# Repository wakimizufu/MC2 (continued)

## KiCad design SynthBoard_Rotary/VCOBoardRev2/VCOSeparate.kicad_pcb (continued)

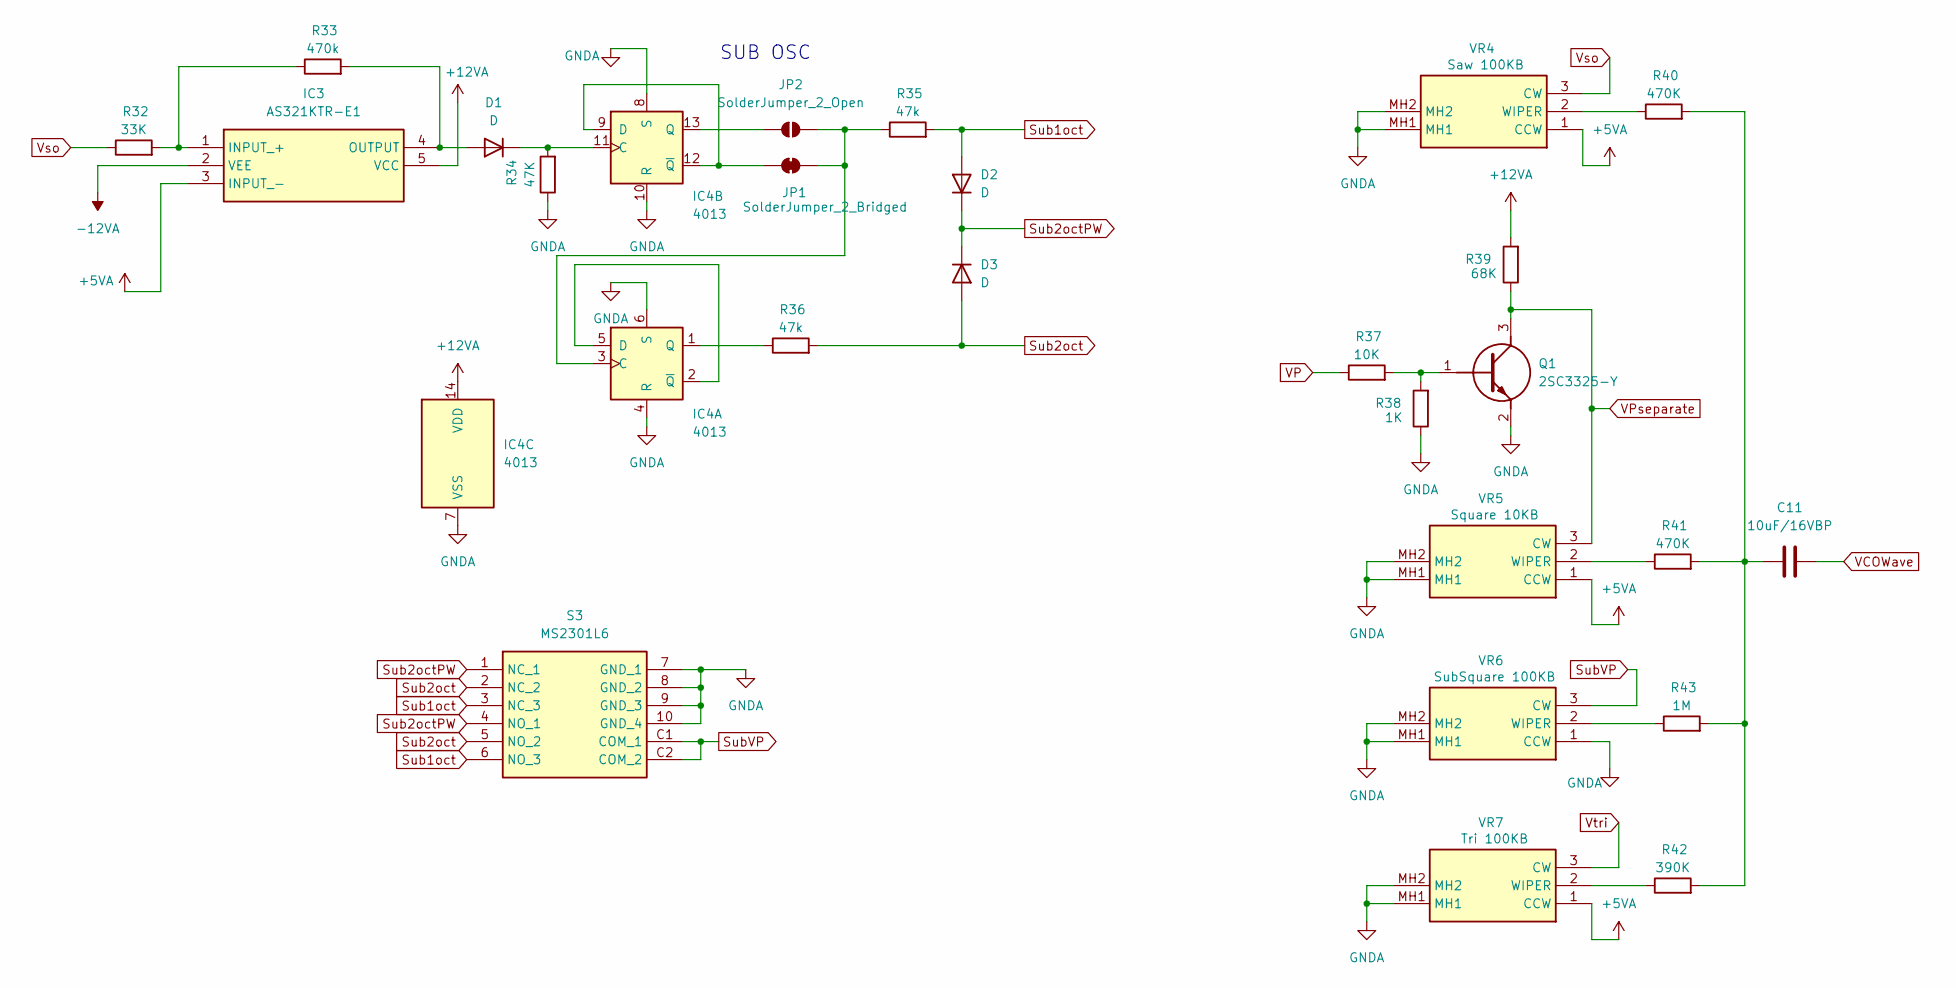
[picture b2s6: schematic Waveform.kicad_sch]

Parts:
C11: 10uF/16VBP; CP_Radial_D5.0mm_P2.50mm
D1, D2, D3: D; D_DO-15_P2.54mm_Vertical_AnodeUp
IC3: AS321KTR-E1; SOT95P282X145-5N; Manufacturer_Part_Number AS321KTR-E1; Mouser Part Number 621-AS321KTR-E1
IC4: 4013; SOIC-14_3.9x8.7mm_P1.27mm
JP1: SolderJumper_2_Bridged; SolderJumper-2_P1.3mm_Bridged2Bar_RoundedPad1.0x1.5mm
JP2: SolderJumper_2_Open; SolderJumper-2_P1.3mm_Open_RoundedPad1.0x1.5mm
Q1: 2SC3325-Y; 2SC3325YLF; Manufacturer_Part_Number 2SC3325-Y
R32: 33K; R_Axial_DIN0207_L6.3mm_D2.5mm_P2.54mm_Vertical
R33: 470k; R_Axial_DIN0207_L6.3mm_D2.5mm_P2.54mm_Vertical
R34: 47K; R_Axial_DIN0207_L6.3mm_D2.5mm_P2.54mm_Vertical
R35, R36: 47k; R_Axial_DIN0207_L6.3mm_D2.5mm_P2.54mm_Vertical
R37: 10K; R_Axial_DIN0207_L6.3mm_D2.5mm_P2.54mm_Vertical
R38: 1K; R_Axial_DIN0207_L6.3mm_D2.5mm_P2.54mm_Vertical
R39: 68K; R_Axial_DIN0207_L6.3mm_D2.5mm_P2.54mm_Vertical
R40, R41: 470K; R_Axial_DIN0207_L6.3mm_D2.5mm_P2.54mm_Vertical
R42: 390K; R_Axial_DIN0207_L6.3mm_D2.5mm_P2.54mm_Vertical
R43: 1M; R_Axial_DIN0207_L6.3mm_D2.5mm_P2.54mm_Vertical
S3: MS2301L6; Manufacturer_Part_Number MS2301L6
VR4: Saw 100KB; RK09D117000B; Manufacturer_Part_Number RK09D117000B; Mouser Part Number 688-RK09D117000B
VR5: Square 10KB; RK09D117000B; Manufacturer_Part_Number RK09D117000B; Mouser Part Number 688-RK09D117000B
VR6: SubSquare 100KB; RK09D117000B; Manufacturer_Part_Number RK09D117000B; Mouser Part Number 688-RK09D117000B
VR7: Tri 100KB; RK09D117000B; Manufacturer_Part_Number RK09D117000B; Mouser Part Number 688-RK09D117000B

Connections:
+5VA: IC3.3 (INPUT_-), VR4.1 (CCW), VR5.1 (CCW), VR7.1 (CCW); also elsewhere on the board
+12VA: IC3.5 (VCC), IC4.14 (VDD), R39.2; also elsewhere on the board
-12VA: IC3.2 (VEE); also elsewhere on the board
GNDA: IC4.4 (R), IC4.6 (S), IC4.7 (VSS), IC4.8 (S), IC4.10 (R), Q1.2 (E), R34.1, R38.1, S3.7 (GND_1), S3.8 (GND_2), S3.9 (GND_3), S3.10 (GND_4), VR4.MH1, VR4.MH2, VR5.MH1, VR5.MH2, VR6.1 (CCW), VR6.MH1, VR6.MH2, VR7.MH1, VR7.MH2; also elsewhere on the board
unnamed: C11.1, R40.2, R41.2, R42.2, R43.2
unnamed: D1.2 (A), IC3.4 (OUTPUT), R33.2
unnamed: D1.1 (K), IC4.11 (C), R34.2
unnamed: IC3.1 (INPUT_+), R32.2, R33.1
unnamed: IC4.3 (C), JP1.2 (B), JP2.2 (B), R35.1
unnamed: IC4.2 (~Q), IC4.5 (D)
unnamed: IC4.1 (Q), R36.1
unnamed: IC4.9 (D), IC4.12 (~Q), JP1.1 (A)
unnamed: IC4.13 (Q), JP2.1 (A)
unnamed: Q1.1 (B), R37.2, R38.2
unnamed: R40.1, VR4.2 (WIPER)
unnamed: R41.1, VR5.2 (WIPER)
unnamed: R43.1, VR6.2 (WIPER)
unnamed: R42.1, VR7.2 (WIPER)
Sub1oct: D2.2 (A), R35.2, S3.3 (NC_3), S3.6 (NO_3)
Sub2oct: D3.2 (A), R36.2, S3.2 (NC_2), S3.5 (NO_2)
Sub2octPW: D2.1 (K), D3.1 (K), S3.1 (NC_1), S3.4 (NO_1)
SubVP: S3.C1 (COM_1), S3.C2 (COM_2), VR6.3 (CW); also elsewhere on the board
VCOWave: C11.2; also elsewhere on the board
VP: R37.1; also elsewhere on the board
VPseparate: Q1.3 (C), R39.1, VR5.3 (CW); also elsewhere on the board
Vso: R32.1, VR4.3 (CW); also elsewhere on the board
Vtri: VR7.3 (CW); also elsewhere on the board

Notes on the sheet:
SUB OSC

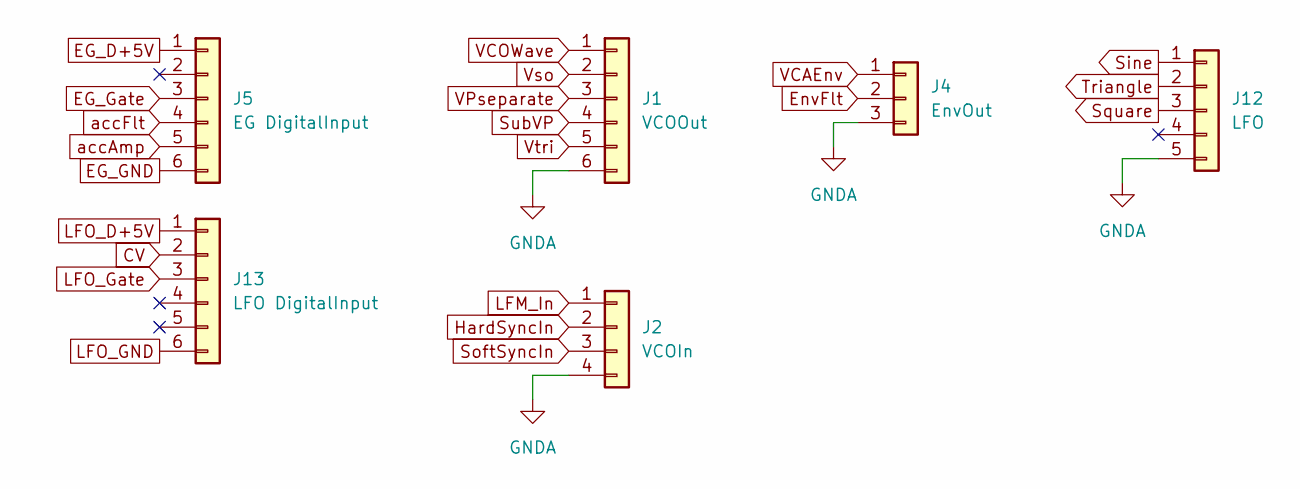
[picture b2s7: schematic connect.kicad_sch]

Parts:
J1: VCOOut; PinSocket_1x06_P2.54mm_Vertical
J2: VCOIn; PinSocket_1x04_P2.54mm_Vertical
J4: EnvOut; PinSocket_1x03_P2.54mm_Vertical
J5: EG DigitalInput; PinSocket_1x06_P2.54mm_Vertical
J12: LFO; PinSocket_1x05_P2.54mm_Vertical
J13: LFO DigitalInput; PinSocket_1x06_P2.54mm_Vertical

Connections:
CV: J13.2; also elsewhere on the board
EG_D+5V: J5.1; also elsewhere on the board
EG_GND: J5.6; also elsewhere on the board
EG_Gate: J5.3; also elsewhere on the board
EnvFlt: J4.2; also elsewhere on the board
GNDA: J1.6, J2.4, J4.3, J12.5; also elsewhere on the board
HardSyncIn: J2.2; also elsewhere on the board
LFM_In: J2.1; also elsewhere on the board
LFO_D+5V: J13.1; also elsewhere on the board
LFO_GND: J13.6; also elsewhere on the board
LFO_Gate: J13.3; also elsewhere on the board
Sine: J12.1; also elsewhere on the board
SoftSyncIn: J2.3; also elsewhere on the board
Square: J12.3; also elsewhere on the board
SubVP: J1.4; also elsewhere on the board
Triangle: J12.2; also elsewhere on the board
VCAEnv: J4.1; also elsewhere on the board
VCOWave: J1.1; also elsewhere on the board
VPseparate: J1.3; also elsewhere on the board
Vso: J1.2; also elsewhere on the board
Vtri: J1.5; also elsewhere on the board
accAmp: J5.5; also elsewhere on the board
accFlt: J5.4; also elsewhere on the board

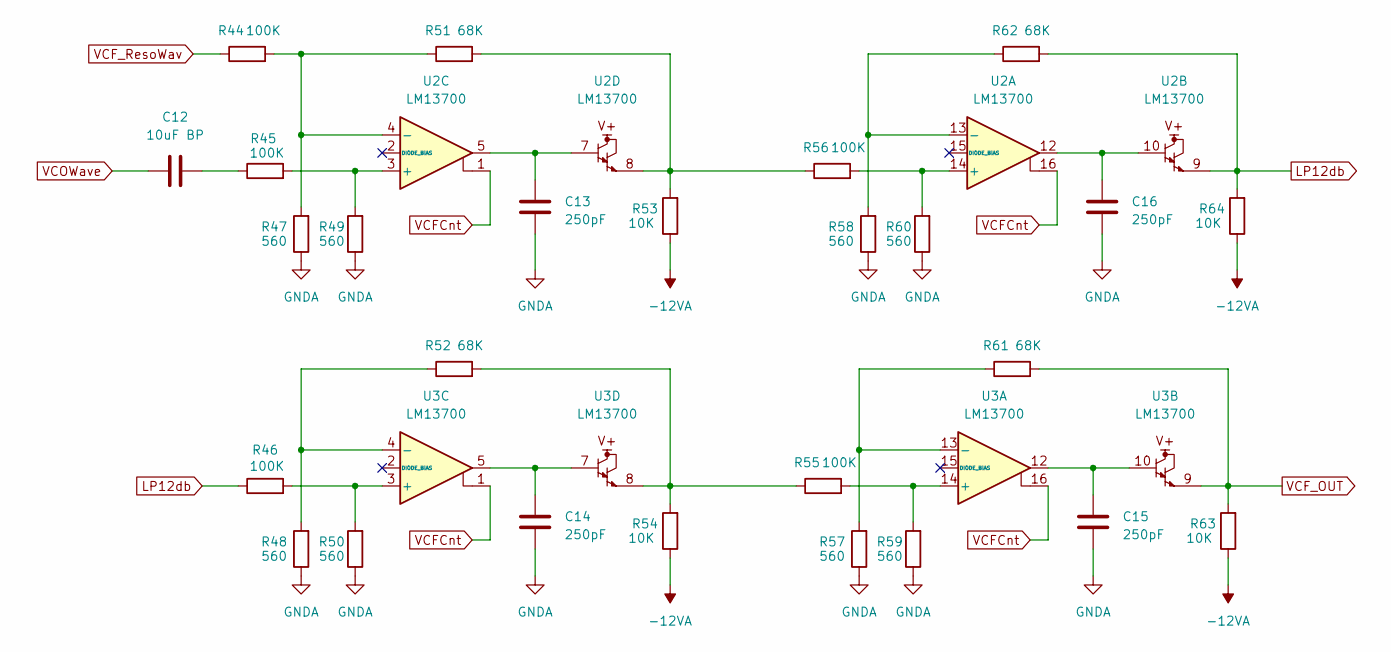
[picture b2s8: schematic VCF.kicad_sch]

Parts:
C12: 10uF BP; CP_Radial_D5.0mm_P2.50mm
C13, C14, C15, C16: 250pF; C_Disc_D5.0mm_W2.5mm_P5.00mm
R44, R45, R46, R55, R56: 100K; R_Axial_DIN0207_L6.3mm_D2.5mm_P2.54mm_Vertical
R47, R48, R49, R50, R57, R58, R59, R60: 560; R_Axial_DIN0207_L6.3mm_D2.5mm_P2.54mm_Vertical
R51, R52, R61, R62: 68K; R_Axial_DIN0207_L6.3mm_D2.5mm_P2.54mm_Vertical
R53, R54, R63, R64: 10K; R_Axial_DIN0207_L6.3mm_D2.5mm_P2.54mm_Vertical
U2, U3: LM13700; SOIC-16_3.9x9.9mm_P1.27mm

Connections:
-12VA: R53.1, R54.1, R63.1, R64.1; also elsewhere on the board
GNDA: C13.2, C14.2, C15.2, C16.2, R47.1, R48.1, R49.1, R50.1, R57.1, R58.1, R59.1, R60.1; also elsewhere on the board
LP12db: R46.1, R62.2, R64.2, U2.9
unnamed: C12.2, R45.1
unnamed: C13.1, U2.5, U2.7
unnamed: C14.1, U3.5, U3.7
unnamed: C15.1, U3.10, U3.12
unnamed: C16.1, U2.10, U2.12
unnamed: R51.2, R53.2, R56.1, U2.8
unnamed: R52.2, R54.2, R55.1, U3.8
unnamed: R56.2, R60.2, U2.14 (+)
unnamed: R58.2, R62.1, U2.13 (-)
unnamed: R45.2, R49.2, U2.3 (+)
unnamed: R44.2, R47.2, R51.1, U2.4 (-)
unnamed: R55.2, R59.2, U3.14 (+)
unnamed: R57.2, R61.1, U3.13 (-)
unnamed: R46.2, R50.2, U3.3 (+)
unnamed: R48.2, R52.1, U3.4 (-)
VCFCnt: U2.1, U2.16, U3.1, U3.16; also elsewhere on the board
VCF_OUT: R61.2, R63.2, U3.9; also elsewhere on the board
VCF_ResoWav: R44.1; also elsewhere on the board
VCOWave: C12.1; also elsewhere on the board

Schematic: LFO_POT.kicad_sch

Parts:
C22, C23, C31: 0.01uF; C_Disc_D4.3mm_W1.9mm_P5.00mm
C24, C25: 47uF/16V; CP_Radial_D5.0mm_P2.50mm
C30: 0.1uF; C_0805_2012Metric_Pad1.18x1.45mm_HandSolder
D4: LED; LED_D5.0mm
IC5: PIC16F15325-I_P; DIP-14_W7.62mm_LongPads; Manufacturer_Part_Number PIC16F15325-I/P; Mouser Part Number 579-PIC16F15325-I/P
IC7: MCP6232T-E/SN; SOIC-8_3.9x4.9mm_P1.27mm; Manufacturer_Part_Number MCP6232-E/P; Mouser Part Number 579-MCP6232-E/P
Q7: 2SC3325-Y; 2SC3325YLF; Manufacturer_Part_Number 2SC3325-Y
R110: 100K; R_Axial_DIN0207_L6.3mm_D2.5mm_P2.54mm_Vertical
R111: 2.2K; R_Axial_DIN0204_L3.6mm_D1.6mm_P2.54mm_Vertical
R113, R114, R118: 10K; R_Axial_DIN0204_L3.6mm_D1.6mm_P2.54mm_Vertical
R115: 30K; R_Axial_DIN0204_L3.6mm_D1.6mm_P2.54mm_Vertical
R116: 20K; R_Axial_DIN0204_L3.6mm_D1.6mm_P2.54mm_Vertical
R117, R119: 100K; R_Axial_DIN0204_L3.6mm_D1.6mm_P2.54mm_Vertical
R120: 1.2K; R_Axial_DIN0204_L3.6mm_D1.6mm_P2.54mm_Vertical
R121, R122, R130: 100; R_Axial_DIN0204_L3.6mm_D1.6mm_P2.54mm_Vertical
R129: 1K; R_Axial_DIN0204_L3.6mm_D1.6mm_P2.54mm_Vertical
U10: Opamp_Dual; SOIC-8_3.9x4.9mm_P1.27mm
VR19: Rate 10KB; RK09D117000B; Manufacturer_Part_Number RK09D117000B; Mouser Part Number 688-RK09D117000B
VR20: Delay 10KB; RK09D117000B; Manufacturer_Part_Number RK09D117000B; Mouser Part Number 688-RK09D117000B

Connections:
+12VA: D4.2 (A), U10.8 (V+); also elsewhere on the board
-12VA: U10.4 (V-); also elsewhere on the board
Delay: IC5.8 (RC2), VR20.2 (WIPER)
GNDA: Q7.2 (E), R116.2, R117.1, R118.1, R119.1; also elsewhere on the board
LFO_D+5V: C30.1, IC5.1 (VDD), IC7.8 (VDD), R129.1, VR19.3 (CW), VR20.3 (CW); also elsewhere on the board
LFO_GND: C22.2, C23.2, C30.2, C31.2, IC5.14 (VSS), IC7.4 (VSS), VR19.1 (CCW), VR19.MH1, VR19.MH2, VR20.1 (CCW), VR20.MH1, VR20.MH2; also elsewhere on the board
LFO_Gate: IC5.10 (RC0); also elsewhere on the board
unnamed: C25.1, R115.2, R116.1
unnamed: C31.1, R129.2, R130.2
unnamed: D4.1 (K), R111.2
unnamed: IC5.4 (VPP/~MCLR/RA3), R130.1
unnamed: C22.1, IC7.3 (VINA+), R113.2
unnamed: C23.1, IC7.5 (VINB+), R114.1
unnamed: Q7.1 (B), R110.2
unnamed: Q7.3 (C), R111.1
unnamed: R120.2, R121.1, U10.7
unnamed: C25.2, R119.2, U10.3 (+)
unnamed: R122.1, U10.1, U10.2 (-)
unnamed: C24.2, R117.2, U10.5 (+)
unnamed: R118.2, R120.1, U10.6 (-)
PWM_Sine: IC5.5 (RC5), R113.1
PWM_Triangle: IC5.6 (RC4), R114.2
Rate: IC5.9 (RC1), VR19.2 (WIPER)
Raw_Sine: IC7.1 (VOUTA), IC7.2 (VINA-), R115.1
Raw_Triangle: C24.1, IC7.6 (VINB-), IC7.7 (VOUTB)
Sine: R122.2; also elsewhere on the board
Square: IC5.11 (RA2); also elsewhere on the board
Triangle: R110.1, R121.2; also elsewhere on the board

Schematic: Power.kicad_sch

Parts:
J7: A_Power; PinHeader_1x06_P2.54mm_Vertical
U1, U6, U8: Opamp_Dual; SOIC-8_3.9x4.9mm_P1.27mm
U2, U3, U5: LM13700; SOIC-16_3.9x9.9mm_P1.27mm

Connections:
+5VA: J7.2; also elsewhere on the board
+12VA: J7.1, U1.8 (V+), U2.11 (V+), U3.11 (V+), U5.11 (V+), U6.8 (V+), U8.8 (V+); also elsewhere on the board
-5VA: J7.3; also elsewhere on the board
-12VA: J7.4, U1.4 (V-), U2.6 (V-), U3.6 (V-), U5.6 (V-), U6.4 (V-), U8.4 (V-); also elsewhere on the board
GNDA: J7.6; also elsewhere on the board

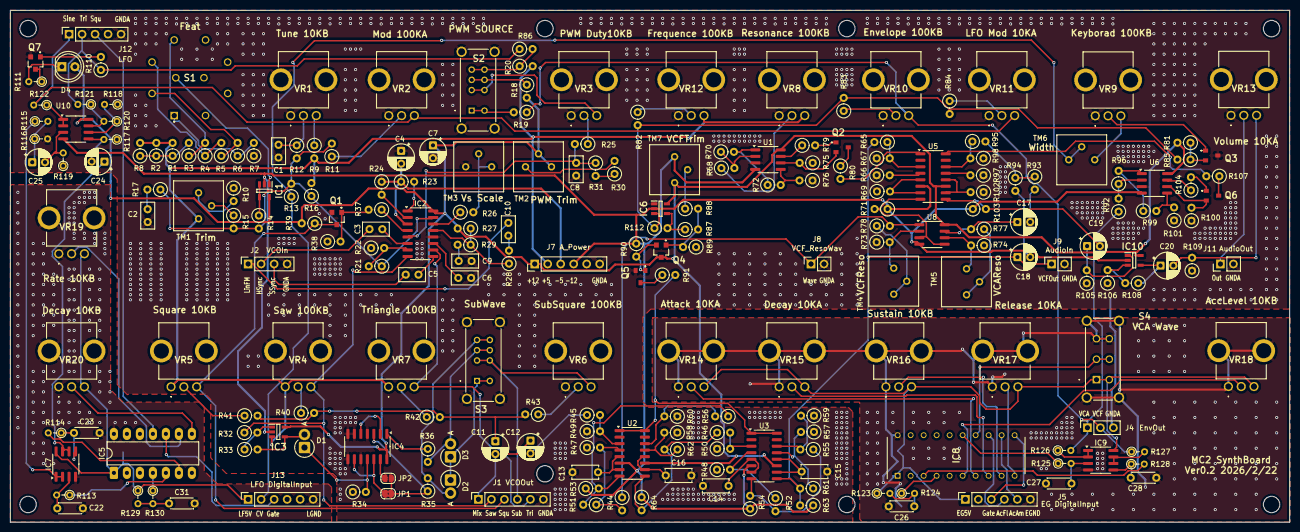
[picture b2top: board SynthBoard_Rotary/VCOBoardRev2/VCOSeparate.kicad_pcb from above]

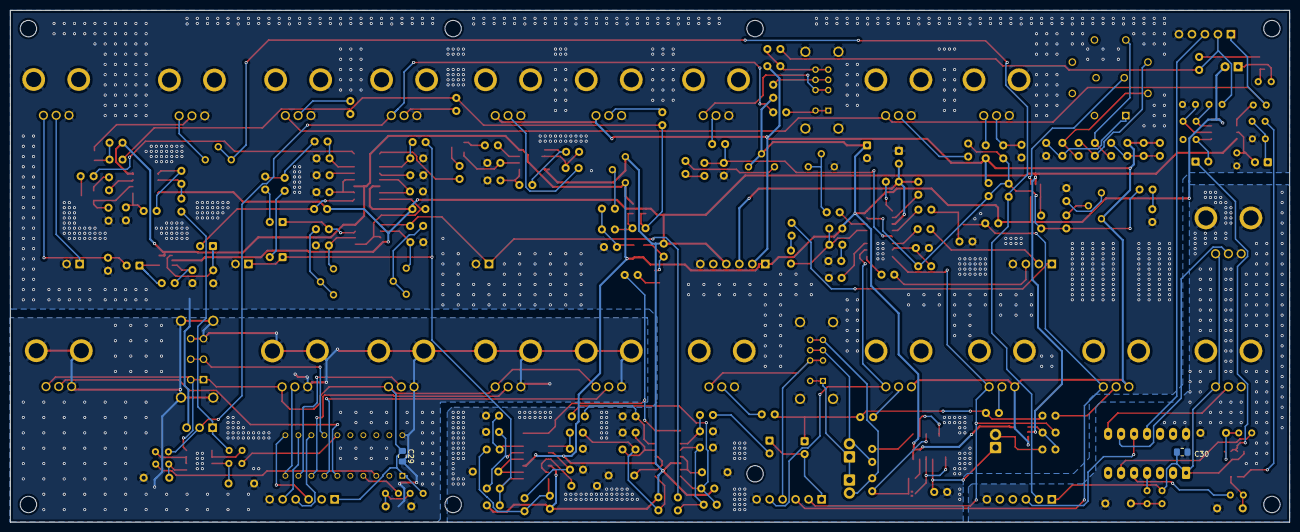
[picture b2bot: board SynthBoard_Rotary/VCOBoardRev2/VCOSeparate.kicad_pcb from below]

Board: 2 copper layers, 250.0 x 100.0 mm, 231 parts (2 on the bottom side), 180 nets.

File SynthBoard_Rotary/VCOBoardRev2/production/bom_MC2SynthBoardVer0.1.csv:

Designator,Footprint,Quantity,Value,LCSC Part #
C1,C_Disc_D5.0mm_W2.5mm_P2.50mm,1,0.001uF,
"C10, C2, C3, C5, C8, C9",C_Disc_D5.0mm_W2.5mm_P2.50mm,6,0.01uF,
C11,CP_Radial_D5.0mm_P2.50mm,1,10uF/16VBP,
C12,CP_Radial_D5.0mm_P2.50mm,1,10uF BP,
"C13, C14, C15, C16",C_Disc_D5.0mm_W2.5mm_P2.50mm,4,250pF,
"C17, C18",CP_Radial_D5.0mm_P2.50mm,2,10uF/25V,
"C19, C20",CP_Radial_D5.0mm_P2.50mm,2,1uF,
"C22, C23, C26, C27, C28, C31",C_Disc_D3.4mm_W2.1mm_P2.50mm,6,0.01uF,
"C24, C25",CP_Radial_D5.0mm_P2.50mm,2,47uF/16V,
"C29, C30",0805,2,0.1uF,
C4,CP_Radial_D5.0mm_P2.50mm,1,2.2uF/50V,
C6,C_Disc_D5.0mm_W2.5mm_P2.50mm,1,1000pF,
C7,CP_Radial_D5.0mm_P2.50mm,1,10uF/16V,
"D1, D2, D3",D_DO-15_P2.54mm_Vertical_AnodeUp,3,D,
D4,LED_D5.0mm,1,LED,
"IC1, IC10, IC3, IC6",SOT95P282X145-5N,4,AS321KTR-E1,
IC2,SOP-16_3.9x9.9mm_P1.27mm,1,V3340M,
IC4,SOIC-14_3.9x8.7mm_P1.27mm,1,4013,
IC5,DIP-14_W7.62mm_LongPads,1,PIC16F15325-I_P,
"IC7, IC9",SOIC-8_3.9x4.9mm_P1.27mm,2,MCP6232T-E/SN,
IC8,DIP794W56P254L2591H533Q20N,1,PIC16F13145-I_P,
J1,PinSocket_1x06_P2.54mm_Vertical,1,VCOOut,
J11,PinHeader_1x02_P2.54mm_Vertical,1,AudioOut,
J12,PinSocket_1x05_P2.54mm_Vertical,1,LFO,
J13,PinSocket_1x06_P2.54mm_Vertical,1,LFO DigitalInput,
J2,PinSocket_1x04_P2.54mm_Vertical,1,VCOIn,
J4,PinSocket_1x03_P2.54mm_Vertical,1,EnvOut,
J5,PinSocket_1x06_P2.54mm_Vertical,1,EG DigitalInput,
J7,PinHeader_1x06_P2.54mm_Vertical,1,A_Power,
J8,PinSocket_1x02_P2.54mm_Vertical,1,VCF_ResoWav,
J9,PinSocket_1x02_P2.54mm_Vertical,1,AudioIn,
"Q1, Q4, Q7",2SC3325YLF,3,2SC3325-Y,
"Q2, Q3, Q5, Q6",1SS294LFT,4,2SA1162-GR_F_,
"R1, R2, R3, R4, R5, R6, R7, R70, R8",R_Axial_DIN0207_L6.3mm_D2.5mm_P2.54mm_Vertical,9,200K,
R10,R_Axial_DIN0207_L6.3mm_D2.5mm_P2.54mm_Vertical,1,270K,
"R100, R101, R104, R38, R75, R76, R77, R79, R89",R_Axial_DIN0207_L6.3mm_D2.5mm_P2.54mm_Vertical,9,1K,
"R102, R106, R107, R112, R19, R22, R37, R53, R54, R63, R64, R65, R69, R72, R73, R74, R78, R9, R91, R94, R95, R99",R_Axial_DIN0207_L6.3mm_D2.5mm_P2.54mm_Vertical,22,10K,
"R103, R71, R80",R_Axial_DIN0207_L6.3mm_D2.5mm_P2.54mm_Vertical,3,5.1K,
"R105, R109, R110, R13, R14, R15, R25, R44, R45, R46, R55, R56, R68, R90, R92, R96",R_Axial_DIN0207_L6.3mm_D2.5mm_P2.54mm_Vertical,16,100K,
"R108, R34, R35, R36, R88, R93",R_Axial_DIN0207_L6.3mm_D2.5mm_P2.54mm_Vertical,6,47K,
R11,R_Axial_DIN0207_L6.3mm_D2.5mm_P2.54mm_Vertical,1,220K,
R111,R_Axial_DIN0204_L3.6mm_D1.6mm_P2.54mm_Vertical,1,2.2K,
"R113, R114, R118, R125, R128",R_Axial_DIN0204_L3.6mm_D1.6mm_P2.54mm_Vertical,5,10K,
R115,R_Axial_DIN0204_L3.6mm_D1.6mm_P2.54mm_Vertical,1,30K,
R116,R_Axial_DIN0204_L3.6mm_D1.6mm_P2.54mm_Vertical,1,20K,
"R117, R119",R_Axial_DIN0204_L3.6mm_D1.6mm_P2.54mm_Vertical,2,100K,
"R12, R28, R43",R_Axial_DIN0207_L6.3mm_D2.5mm_P2.54mm_Vertical,3,1M,
R120,R_Axial_DIN0204_L3.6mm_D1.6mm_P2.54mm_Vertical,1,1.2K,
"R121, R122, R124, R126, R127, R130",R_Axial_DIN0204_L3.6mm_D1.6mm_P2.54mm_Vertical,6,100,
"R123, R129",R_Axial_DIN0204_L3.6mm_D1.6mm_P2.54mm_Vertical,2,1K,
R16,R_Axial_DIN0207_L6.3mm_D2.5mm_P2.54mm_Vertical,1,560K,
"R17, R29, R47, R48, R49, R50, R57, R58, R59, R60, R66, R67, R97, R98",R_Axial_DIN0207_L6.3mm_D2.5mm_P2.54mm_Vertical,14,560,
R18,R_Axial_DIN0207_L6.3mm_D2.5mm_P2.54mm_Vertical,1,50K,
"R20, R32, R81",R_Axial_DIN0207_L6.3mm_D2.5mm_P2.54mm_Vertical,3,33K,
"R21, R27",R_Axial_DIN0207_L6.3mm_D2.5mm_P2.54mm_Vertical,2,1.5M,
R23,R_Axial_DIN0207_L6.3mm_D2.5mm_P2.54mm_Vertical,1,28K,
R24,R_Axial_DIN0207_L6.3mm_D2.5mm_P2.54mm_Vertical,1,5.6K,
R26,R_Axial_DIN0207_L6.3mm_D2.5mm_P2.54mm_Vertical,1,1.8K,
"R30, R83",R_Axial_DIN0207_L6.3mm_D2.5mm_P2.54mm_Vertical,2,56K,
"R31, R42",R_Axial_DIN0207_L6.3mm_D2.5mm_P2.54mm_Vertical,2,390K,
"R33, R40, R41",R_Axial_DIN0207_L6.3mm_D2.5mm_P2.54mm_Vertical,3,470k,
"R39, R51, R52, R61, R62",R_Axial_DIN0207_L6.3mm_D2.5mm_P2.54mm_Vertical,5,68K,
R82,R_Axial_DIN0207_L6.3mm_D2.5mm_P2.54mm_Vertical,1,20K,
R84,R_Axial_DIN0207_L6.3mm_D2.5mm_P2.54mm_Vertical,1,39K,
R85,R_Axial_DIN0207_L6.3mm_D2.5mm_P2.54mm_Vertical,1,150K,
R87,R_Axial_DIN0207_L6.3mm_D2.5mm_P2.54mm_Vertical,1,27K,
S1,RS164POS2POL,1,RS16-4POS-2POL,
"S2, S3",MS2301L6,2,MS2301L6,
S4,MS2201L6,1,MS2201L6,
"TM1, TM2, TM6",Potentiometer_Bourns_3386P_Vertical,3,3386P 50K,
TM3,Potentiometer_Bourns_3386P_Vertical,1,3386P 500,
"TM4, TM5",Potentiometer_Bourns_3386P_Vertical,2,3386P 10K,
TM7,Potentiometer_Bourns_3386P_Vertical,1,3386P 100K,
"U1, U10, U6, U8",SOIC-8_3.9x4.9mm_P1.27mm,4,Opamp_Dual,
"U2, U3, U5",SOIC-16_3.9x9.9mm_P1.27mm,3,LM13700,
VR1,RK09D117000B,1,Tune 10KB,
VR10,RK09D117000B,1,VCF Env100KB,
VR11,RK09D117000B,1,VCF LFO100KA,
VR12,RK09D117000B,1,VCF FREQ 100KB,
VR13,RK09D117000B,1,AudioOut 100KA,
VR14,RK09D117000B,1,Attack 10KA,
VR15,RK09D117000B,1,Decay 10KA,
VR16,RK09D117000B,1,Sustain 10KB,
VR17,RK09D117000B,1,Release 10KA,
VR18,RK09D117000B,1,AccLevel 10KB,
VR19,RK09D117000B,1,Rate 10KB,
VR2,RK09D117000B,1,Mod 100KA,
VR20,RK09D117000B,1,Delay 10KB,
VR3,RK09D117000B,1,PWM Duty10KB,
VR4,RK09D117000B,1,Saw 100KB,
VR5,RK09D117000B,1,Square 10KB,
VR6,RK09D117000B,1,SubSquare 100KB,
VR7,RK09D117000B,1,Tri 100KB,
VR8,RK09D117000B,1,VCF Resonance 100KB,
VR9,RK09D117000B,1,VCF KYBD100KB,

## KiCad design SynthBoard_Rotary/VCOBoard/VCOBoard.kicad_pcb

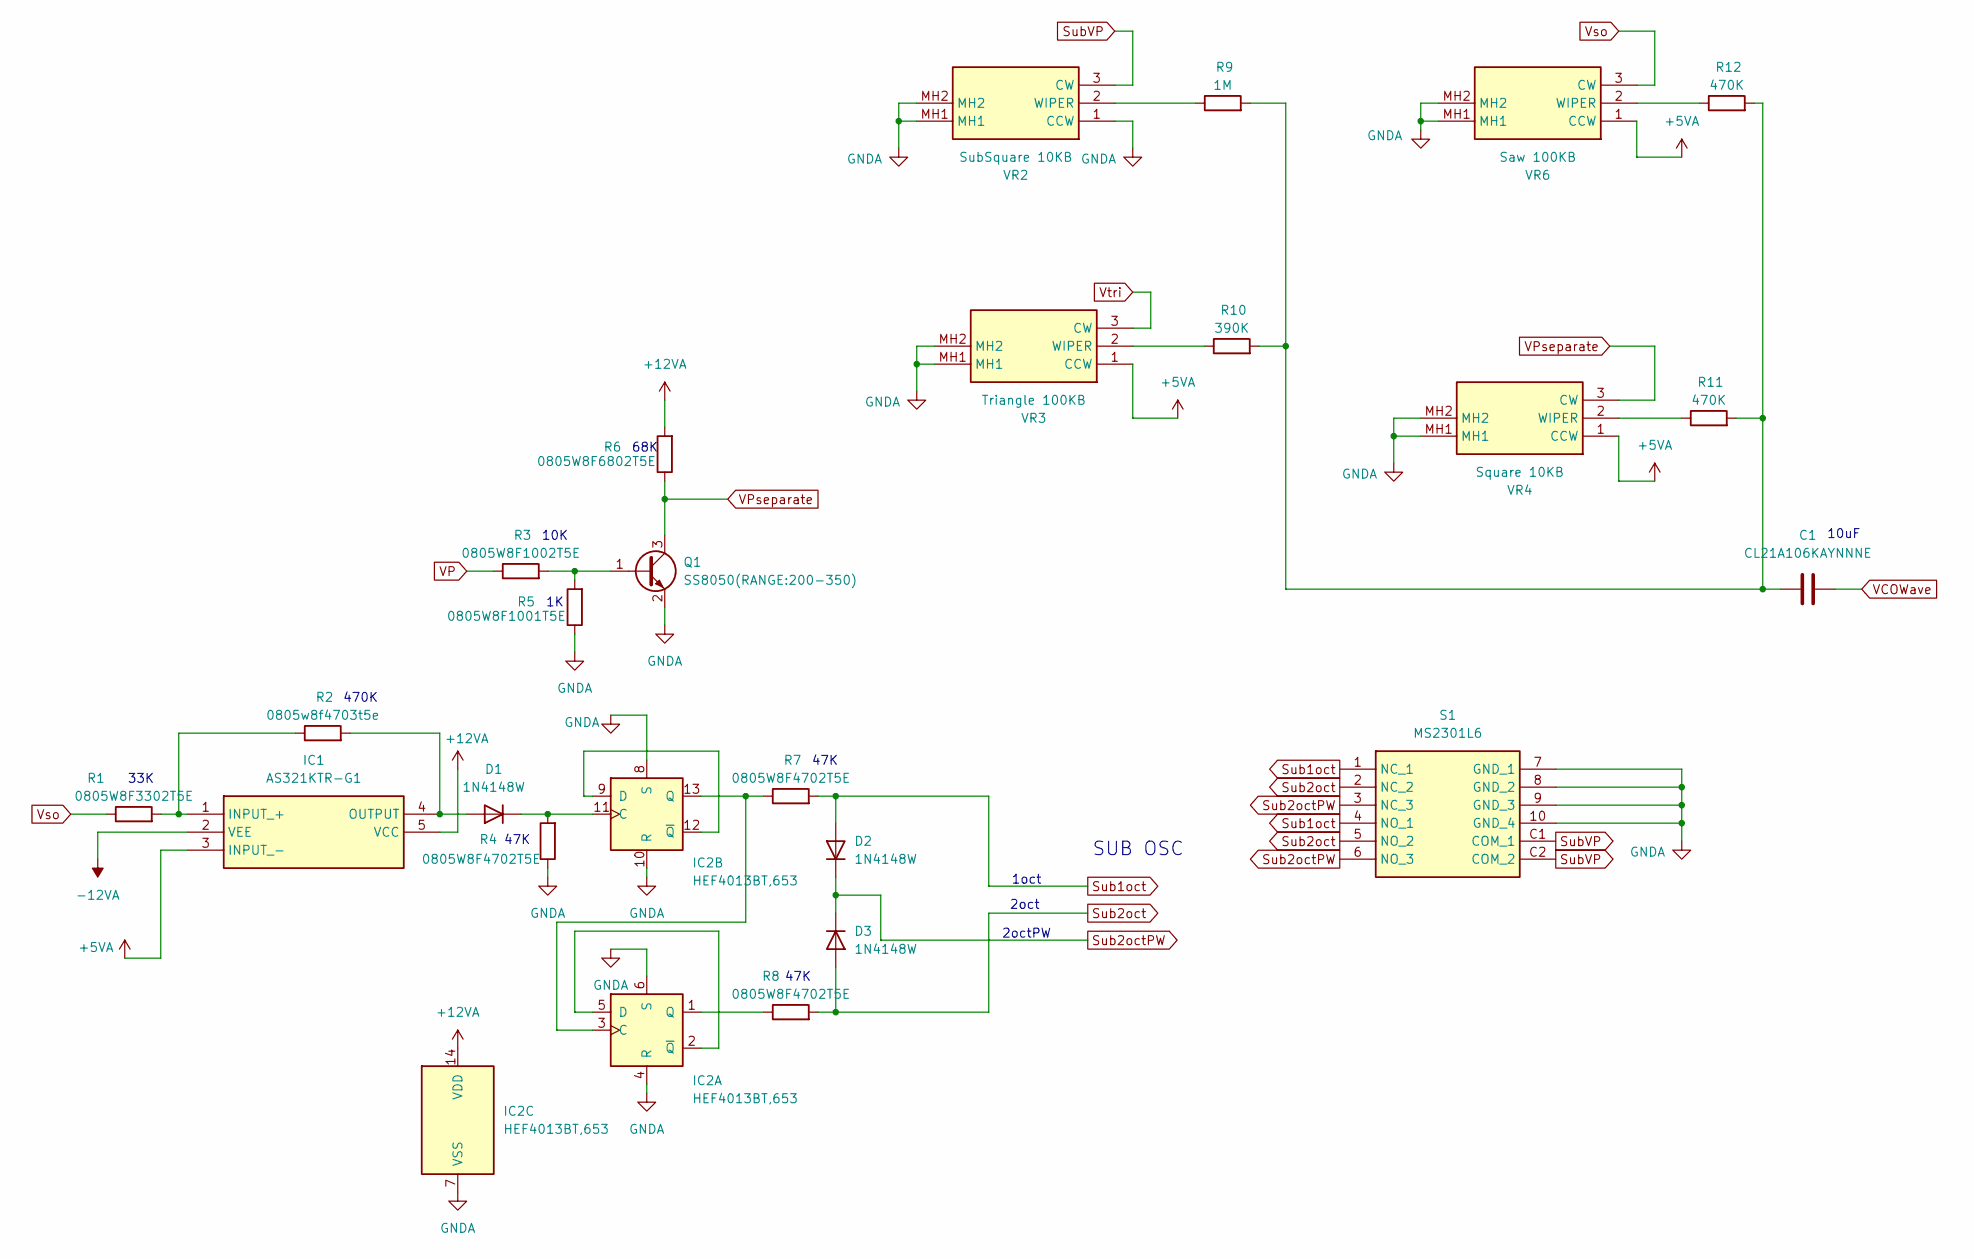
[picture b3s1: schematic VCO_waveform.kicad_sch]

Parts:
C1: CL21A106KAYNNNE; C_0805_2012Metric_Pad1.18x1.45mm_HandSolder
D1, D2, D3: 1N4148W; D_SOD-123
IC1: AS321KTR-G1; SOT95P282X145-5N; Manufacturer_Part_Number AS321KTR-E1; Mouser Part Number 621-AS321KTR-E1
IC2: HEF4013BT,653; SOIC-14_3.9x8.7mm_P1.27mm
Q1: SS8050(RANGE:200-350); SOT95P240X115-3N
R1: 0805W8F3302T5E; R_0805_2012Metric_Pad1.20x1.40mm_HandSolder
R2: 0805w8f4703t5e; R_0805_2012Metric_Pad1.20x1.40mm_HandSolder
R3: 0805W8F1002T5E; R_0805_2012Metric_Pad1.20x1.40mm_HandSolder
R4, R7, R8: 0805W8F4702T5E; R_0805_2012Metric_Pad1.20x1.40mm_HandSolder
R5: 0805W8F1001T5E; R_0805_2012Metric_Pad1.20x1.40mm_HandSolder
R6: 0805W8F6802T5E; R_0805_2012Metric_Pad1.20x1.40mm_HandSolder
R9: 1M; R_Axial_DIN0207_L6.3mm_D2.5mm_P7.62mm_Horizontal
R10: 390K; R_Axial_DIN0207_L6.3mm_D2.5mm_P7.62mm_Horizontal
R11, R12: 470K; R_Axial_DIN0207_L6.3mm_D2.5mm_P7.62mm_Horizontal
S1: MS2301L6; Manufacturer_Part_Number MS2301L6
VR2: SubSquare 10KB; RK09D117000B; Manufacturer_Part_Number RK09D117000B; Mouser Part Number 688-RK09D117000B
VR3: Triangle 100KB; RK09D117000B; Manufacturer_Part_Number RK09D117000B; Mouser Part Number 688-RK09D117000B
VR4: Square 10KB; RK09D117000B; Manufacturer_Part_Number RK09D117000B; Mouser Part Number 688-RK09D117000B
VR6: Saw 100KB; RK09D117000B; Manufacturer_Part_Number RK09D117000B; Mouser Part Number 688-RK09D117000B

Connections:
+5VA: IC1.3 (INPUT_-), VR3.1 (CCW), VR4.1 (CCW), VR6.1 (CCW); also elsewhere on the board
+12VA: IC1.5 (VCC), IC2.14 (VDD), R6.2; also elsewhere on the board
-12VA: IC1.2 (VEE); also elsewhere on the board
GNDA: IC2.4 (R), IC2.6 (S), IC2.7 (VSS), IC2.8 (S), IC2.10 (R), Q1.2 (E), R4.1, R5.1, S1.7 (GND_1), S1.8 (GND_2), S1.9 (GND_3), S1.10 (GND_4), VR2.1 (CCW), VR2.MH1, VR2.MH2, VR3.MH1, VR3.MH2, VR4.MH1, VR4.MH2, VR6.MH1, VR6.MH2; also elsewhere on the board
unnamed: C1.1, R9.2, R10.2, R11.2, R12.2
unnamed: D1.2 (A), IC1.4 (OUTPUT), R2.2
unnamed: D1.1 (K), IC2.11 (C), R4.2
unnamed: IC1.1 (INPUT_+), R1.2, R2.1
unnamed: IC2.3 (C), IC2.13 (Q), R7.1
unnamed: IC2.2 (~Q), IC2.5 (D)
unnamed: IC2.1 (Q), R8.1
unnamed: IC2.9 (D), IC2.12 (~Q)
unnamed: Q1.1 (B), R3.2, R5.2
unnamed: R9.1, VR2.2 (WIPER)
unnamed: R10.1, VR3.2 (WIPER)
unnamed: R11.1, VR4.2 (WIPER)
unnamed: R12.1, VR6.2 (WIPER)
Sub1oct: D2.2 (A), R7.2, S1.1 (NC_1), S1.4 (NO_1)
Sub2oct: D3.2 (A), R8.2, S1.2 (NC_2), S1.5 (NO_2)
Sub2octPW: D2.1 (K), D3.1 (K), S1.3 (NC_3), S1.6 (NO_3)
SubVP: S1.C1 (COM_1), S1.C2 (COM_2), VR2.3 (CW); also elsewhere on the board
VCOWave: C1.2; also elsewhere on the board
VP: R3.1; also elsewhere on the board
VPseparate: Q1.3 (C), R6.1, VR4.3 (CW); also elsewhere on the board
Vso: R1.1, VR6.3 (CW); also elsewhere on the board
Vtri: VR3.3 (CW); also elsewhere on the board

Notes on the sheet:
47K
1oct
33K
SUB OSC
10K
2octPW
2oct
10uF
470K
68K

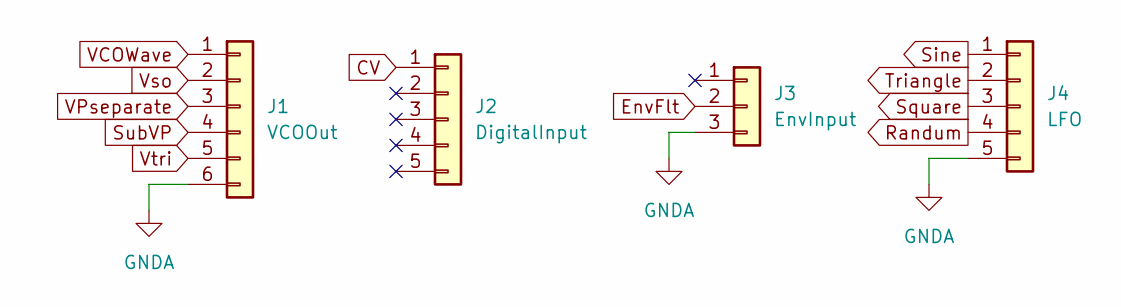
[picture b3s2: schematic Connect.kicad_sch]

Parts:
J1: VCOOut; PinSocket_1x06_P2.54mm_Vertical
J2: DigitalInput; PinHeader_1x05_P2.54mm_Vertical
J3: EnvInput; PinSocket_1x03_P2.54mm_Vertical
J4: LFO; PinSocket_1x05_P2.54mm_Vertical

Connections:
CV: J2.1; also elsewhere on the board
EnvFlt: J3.2; also elsewhere on the board
GNDA: J1.6, J3.3, J4.5; also elsewhere on the board
Randum: J4.4
Sine: J4.1; also elsewhere on the board
Square: J4.3
SubVP: J1.4; also elsewhere on the board
Triangle: J4.2; also elsewhere on the board
VCOWave: J1.1; also elsewhere on the board
VPseparate: J1.3; also elsewhere on the board
Vso: J1.2; also elsewhere on the board
Vtri: J1.5; also elsewhere on the board
